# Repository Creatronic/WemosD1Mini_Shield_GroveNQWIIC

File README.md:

# WemosD1Mini_Shield_GroveNQWIIC
Shield for Wemos D1 Mini and D1 ESP32 boards which allow connecting Grove and QWIIC modules

More information (in french) => https://blog.creatronic.fr/ghost/#/editor/post/5ff040666ba80f01855d5f61

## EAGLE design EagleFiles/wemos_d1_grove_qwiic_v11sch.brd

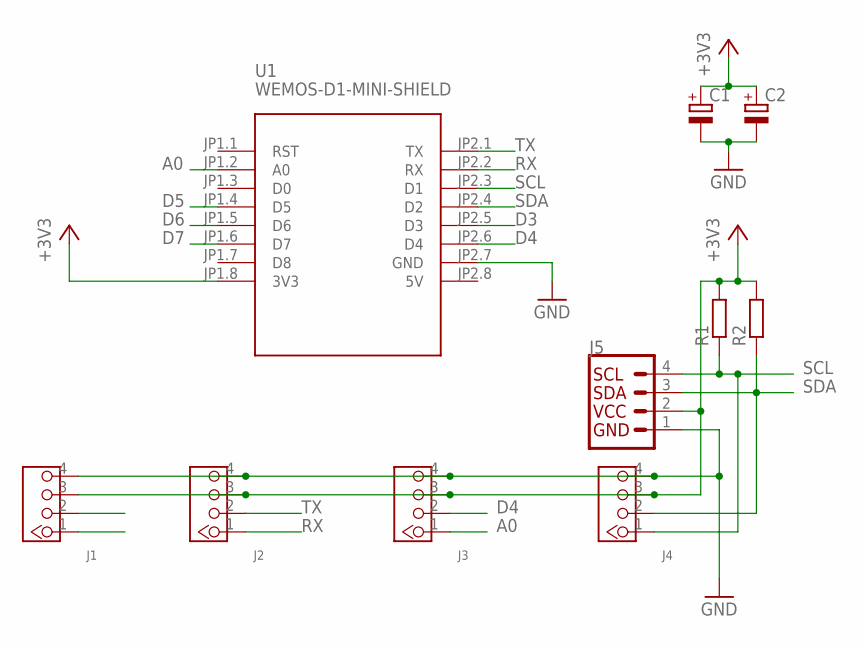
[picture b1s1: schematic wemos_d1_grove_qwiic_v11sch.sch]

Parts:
C1: CPOL-EU153CLV-0505; 153CLV-0505
C2: CPOL-EUCT3528; CT3528
J1, J2, J3, J4: 4P-2.0; HW4-2.0
J5: QWIIC_CONNECTORJS-1MM; 1X04_1MM_RA
R1, R2: R-EU_R0603; R0603
U1: WEMOS-D1-MINI-SHIELD

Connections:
5V: U1.JP2.8 (5V)
+3V3: C1.+, C2.+, J1.3, J2.3, J3.3, J4.3, J5.2 (VCC), R1.2, R2.2, U1.JP1.8 (3V3)
A0: J3.1, U1.JP1.2 (A0)
D3: U1.JP2.5 (D3)
D4: J3.2, U1.JP2.6 (D4)
D5: J1.1, U1.JP1.4 (D5)
D6: J1.2, U1.JP1.5 (D6)
D7: U1.JP1.6 (D7)
GND: C1.-, C2.-, J1.4, J2.4, J3.4, J4.4, J5.1 (GND), U1.JP2.7 (GND)
RX: J2.1, U1.JP2.2 (RX)
SCL: J4.1, J5.4 (SCL), R1.1, U1.JP2.3 (D1)
SDA: J4.2, J5.3 (SDA), R2.1, U1.JP2.4 (D2)
TX: J2.2, U1.JP2.1 (TX)

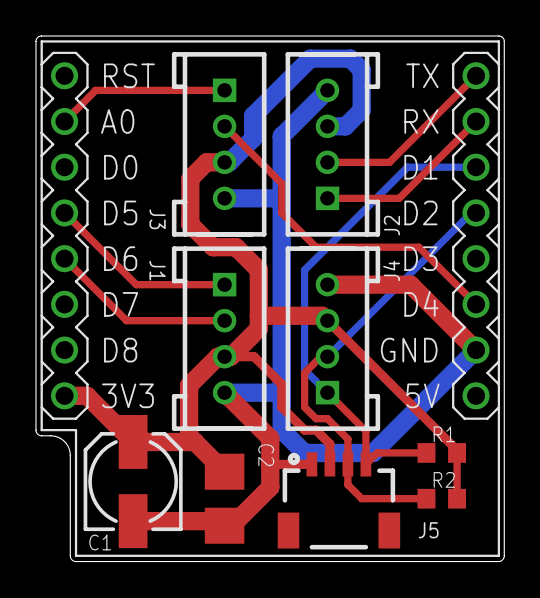
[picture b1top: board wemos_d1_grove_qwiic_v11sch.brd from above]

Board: 2 copper layers, 26.0 x 29.2 mm, 10 parts (0 on the bottom side), 10 nets.

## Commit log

2021-02-28 Rename wemos_d1_grove_qwiic_v11sch.DRD to Gerber/wemos_d1_grove_qwiic_v11sch.DRD
2021-02-28 Rename wemos_d1_grove_qwiic_v11sch.brd to EagleFiles/wemos_d1_grove_qwiic_v11sch.brd
2021-02-28 Rename Eaglewemos_d1_grove_qwiic_v11sch.sch to EagleFiles/wemos_d1_grove_qwiic_v11sch.sch

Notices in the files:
parts and their libraries:
SparkFun-Connectors: Licensing: Creative Commons ShareAlike 4.0 International - https://creativecommons.org/licenses/by-sa/4.0
diy-modules: Released under the Creative Commons Attribution 4.0 International License: http://creativecommons.org/licenses/by/4.0
